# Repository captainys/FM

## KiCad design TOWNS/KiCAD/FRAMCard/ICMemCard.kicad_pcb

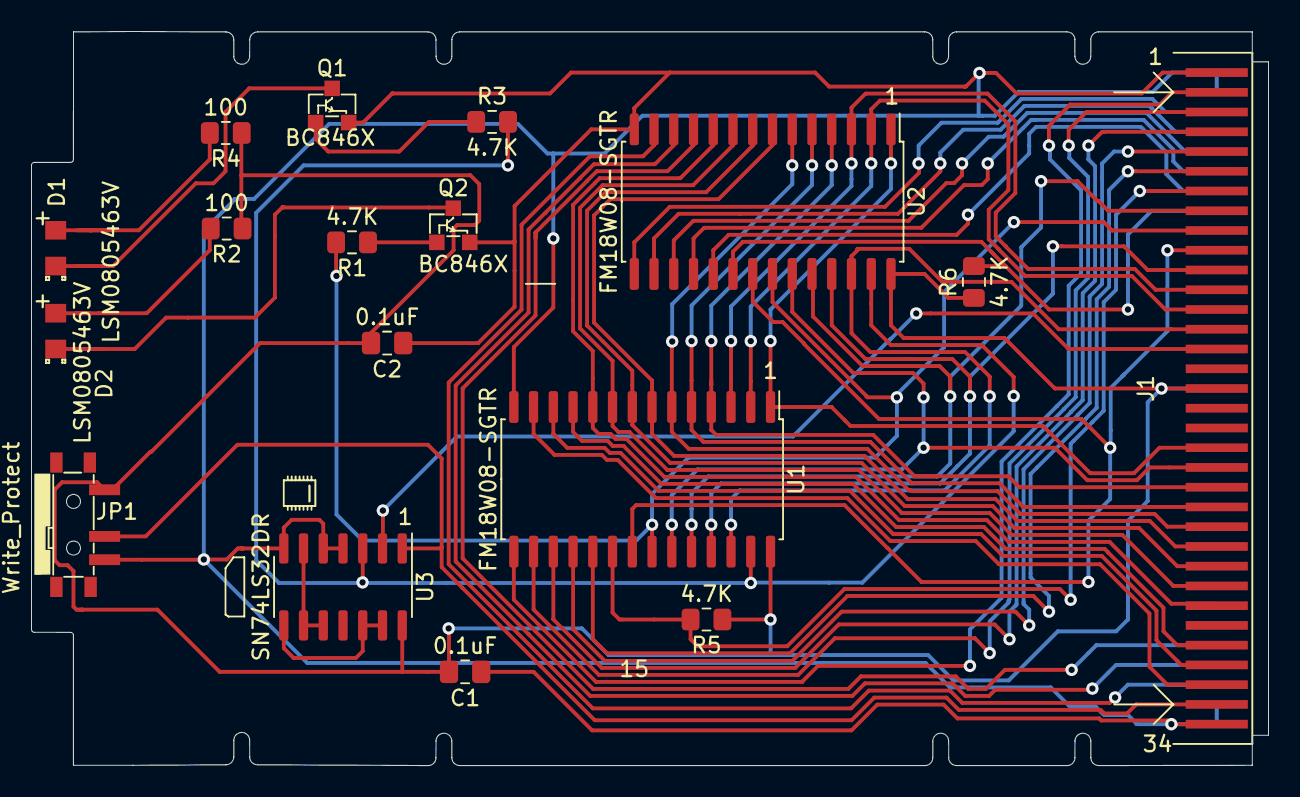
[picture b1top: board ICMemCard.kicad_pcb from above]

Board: 2 copper layers, 79.6 x 47.2 mm, 17 parts (0 on the bottom side), 47 nets.

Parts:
C1, C2: 0.1uF; C_0805_2012Metric_Pad1.18x1.45mm_HandSolder
D1, D2: LSM0805463V
J1: PCMCIA_Connector; PCMCIA_2x34_FrontBack
JP1: Write_Protect; MA_Memory_Card_Slide_Switch
Q1, Q2: BC846X; BC846X_AU_Q_NPN_BCE
R1, R3, R5, R6: 4.7K; R_0805_2012Metric_Pad1.15x1.40mm_HandSolder
R2, R4: 100; R_0805_2012Metric_Pad1.15x1.40mm_HandSolder
U1, U2: FM18W08-SGTR; SOIC-28W_7.5x17.9mm_P1.27mm
U3: SN74LS32DR; SOIC-14_3.9x8.7mm_P1.27mm

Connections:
/A1: J1.28, U1.10, U2.10
/A2: J1.27, U1.9, U2.9
/A3: J1.26, U1.8, U2.8
/A4: J1.25, U1.7, U2.7
/A5: J1.24, U1.6, U2.6
/A6: J1.23, U1.5, U2.5
/A7: J1.22, U1.4, U2.4
/A8: J1.12, U1.3, U2.3
/A9: J1.11, U1.25, U2.25
/A10: J1.8, U1.24, U2.24
/A11: J1.10, U1.21, U2.21
/A12: J1.21, U1.23, U2.23
/A13: J1.13, U1.2, U2.2
/A14: J1.14, U1.26, U2.26
/A15: J1.20, U1.1, U2.1
/D0: J1.30, U1.11
/D1: J1.31, U1.12
/D2: J1.32, U1.13
/D3: J1.2, U1.15
/D4: J1.3, U1.16
/D5: J1.4, U1.17
/D6: J1.5, U1.18
/D7: J1.6, U1.19
/D8: J1.64, U2.11
/D9: J1.65, U2.12
/D10: J1.66, U2.13
/D11: J1.37, U2.15
/D12: J1.38, U2.16
/D13: J1.39, U2.17
/D14: J1.40, U2.18
/D15: J1.41, U2.19
/WP: J1.33, JP1.2, U3.1
/~CE1: J1.7, R5.2, U1.20
/~CE2: J1.42, R6.2, U2.20
/~OE: J1.9, R1.2, U1.22, U2.22
/~WE: J1.15, U3.2
/~WEorWP: R3.2, U1.27, U2.27, U3.3
GND: C1.1, C2.1, J1.1, J1.34, J1.35, J1.36, J1.67, J1.68, JP1.1, Q1.3, Q2.3, U1.14, U2.14, U3.4, U3.5, U3.7
unnamed: D1.1, Q1.2
unnamed: D1.2, R4.2
unnamed: D2.1, Q2.2
unnamed: D2.2, R2.2
unnamed: Q1.1, R3.1
unnamed: Q2.1, R1.1
unnamed: U3.6, U3.9, U3.10
unnamed: U3.8, U3.12, U3.13
Vcc: C1.2, C2.2, J1.17, J1.51, JP1.3, R2.1, R4.1, R5.1, R6.1, U1.28, U2.28, U3.14

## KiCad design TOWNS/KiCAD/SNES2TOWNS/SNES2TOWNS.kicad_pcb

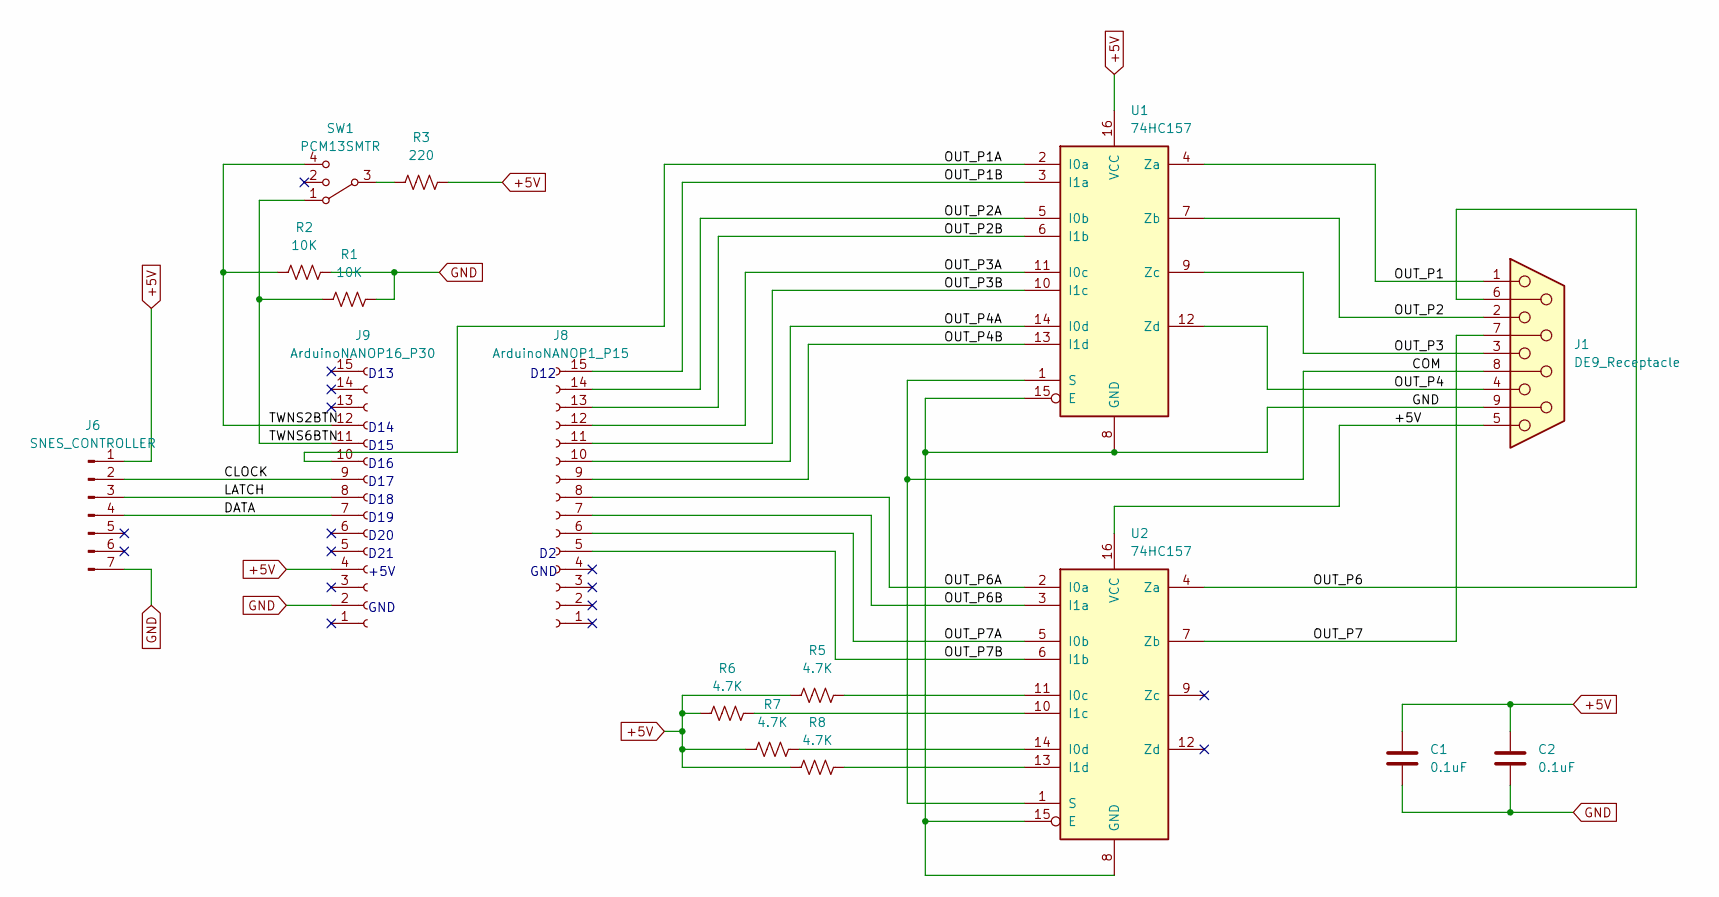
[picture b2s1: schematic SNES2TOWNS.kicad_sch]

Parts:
C1, C2: 0.1uF; C_0805_2012Metric_Pad1.18x1.45mm_HandSolder
J1: DE9_Receptacle; DSUB-9_Female_Vertical_P2.77x2.84mm
J6: SNES_CONTROLLER; SNES_Controller
J8: ArduinoNANOP1_P15; PinSocket_1x15_P2.54mm_Vertical
J9: ArduinoNANOP16_P30; PinSocket_1x15_P2.54mm_Vertical
R1, R2: 10K; R_0805_2012Metric_Pad1.20x1.40mm_HandSolder
R3: 220; R_0805_2012Metric_Pad1.20x1.40mm_HandSolder
R5, R6, R7, R8: 4.7K; R_0805_2012Metric_Pad1.20x1.40mm_HandSolder
SW1: PCM13SMTR; SW_SP3T_PCM13
U1, U2: 74HC157; DIP-16_W7.62mm_Socket

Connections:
+5V: C1.1, C2.1, J1.5, J6.1, J9.4, R3.2, R5.1, R6.1, R7.1, R8.1, U1.16 (VCC), U2.16 (VCC)
/CLOCK: J6.2, J9.9
/COM: J1.8, U1.1 (S), U2.1 (S)
/DATA: J6.4, J9.7
/LATCH: J6.3, J9.8
/OUT_P1: J1.1, U1.4 (Za)
/OUT_P1A: J9.10, U1.2 (I0a)
/OUT_P1B: J8.15, U1.3 (I1a)
/OUT_P2: J1.2, U1.7 (Zb)
/OUT_P2A: J8.14, U1.5 (I0b)
/OUT_P2B: J8.13, U1.6 (I1b)
/OUT_P3: J1.3, U1.9 (Zc)
/OUT_P3A: J8.12, U1.11 (I0c)
/OUT_P3B: J8.11, U1.10 (I1c)
/OUT_P4: J1.4, U1.12 (Zd)
/OUT_P4A: J8.10, U1.14 (I0d)
/OUT_P4B: J8.9, U1.13 (I1d)
/OUT_P6: J1.6, U2.4 (Za)
/OUT_P6A: J8.8, U2.2 (I0a)
/OUT_P6B: J8.7, U2.3 (I1a)
/OUT_P7: J1.7, U2.7 (Zb)
/OUT_P7A: J8.6, U2.5 (I0b)
/OUT_P7B: J8.5, U2.6 (I1b)
/TWNS2BTN: J9.12, R2.1, SW1.4
/TWNS6BTN: J9.11, R1.1, SW1.1
GND: C1.2, C2.2, J1.9, J6.7, J9.2, R1.2, R2.2, U1.8 (GND), U1.15 (E), U2.8 (GND), U2.15 (E)
unnamed: R3.1, SW1.3
unnamed: R5.2, U2.11 (I0c)
unnamed: R7.2, U2.14 (I0d)
unnamed: R6.2, U2.10 (I1c)
unnamed: R8.2, U2.13 (I1d)

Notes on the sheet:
GND
D20
D12
D19
D14
D16
D18
D13
D21
D17
+5V
D15

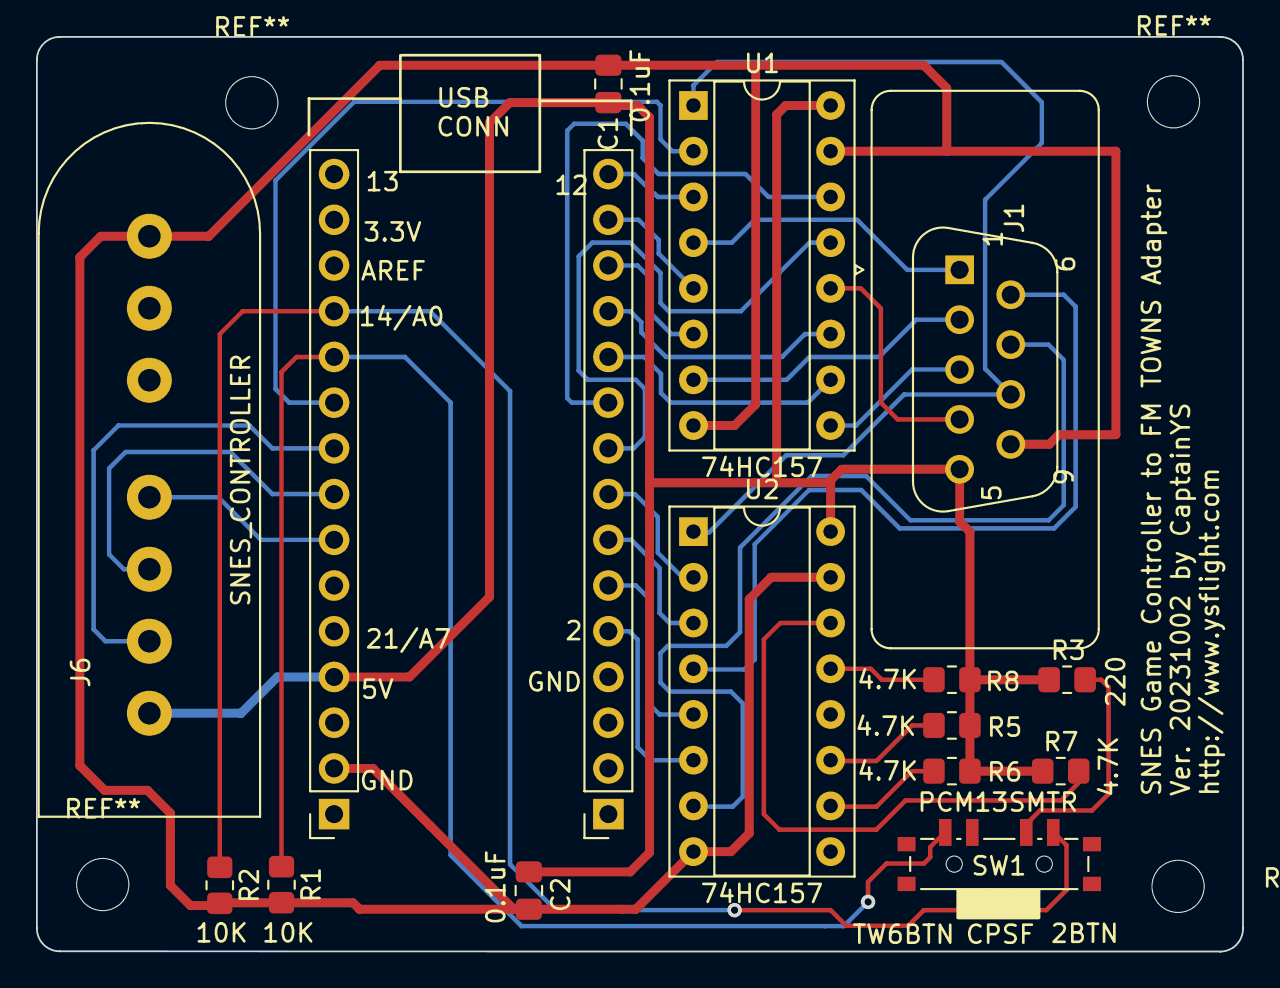
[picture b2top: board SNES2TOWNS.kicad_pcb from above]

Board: 2 copper layers, 67.0 x 50.8 mm, 16 parts (0 on the bottom side), 31 nets.

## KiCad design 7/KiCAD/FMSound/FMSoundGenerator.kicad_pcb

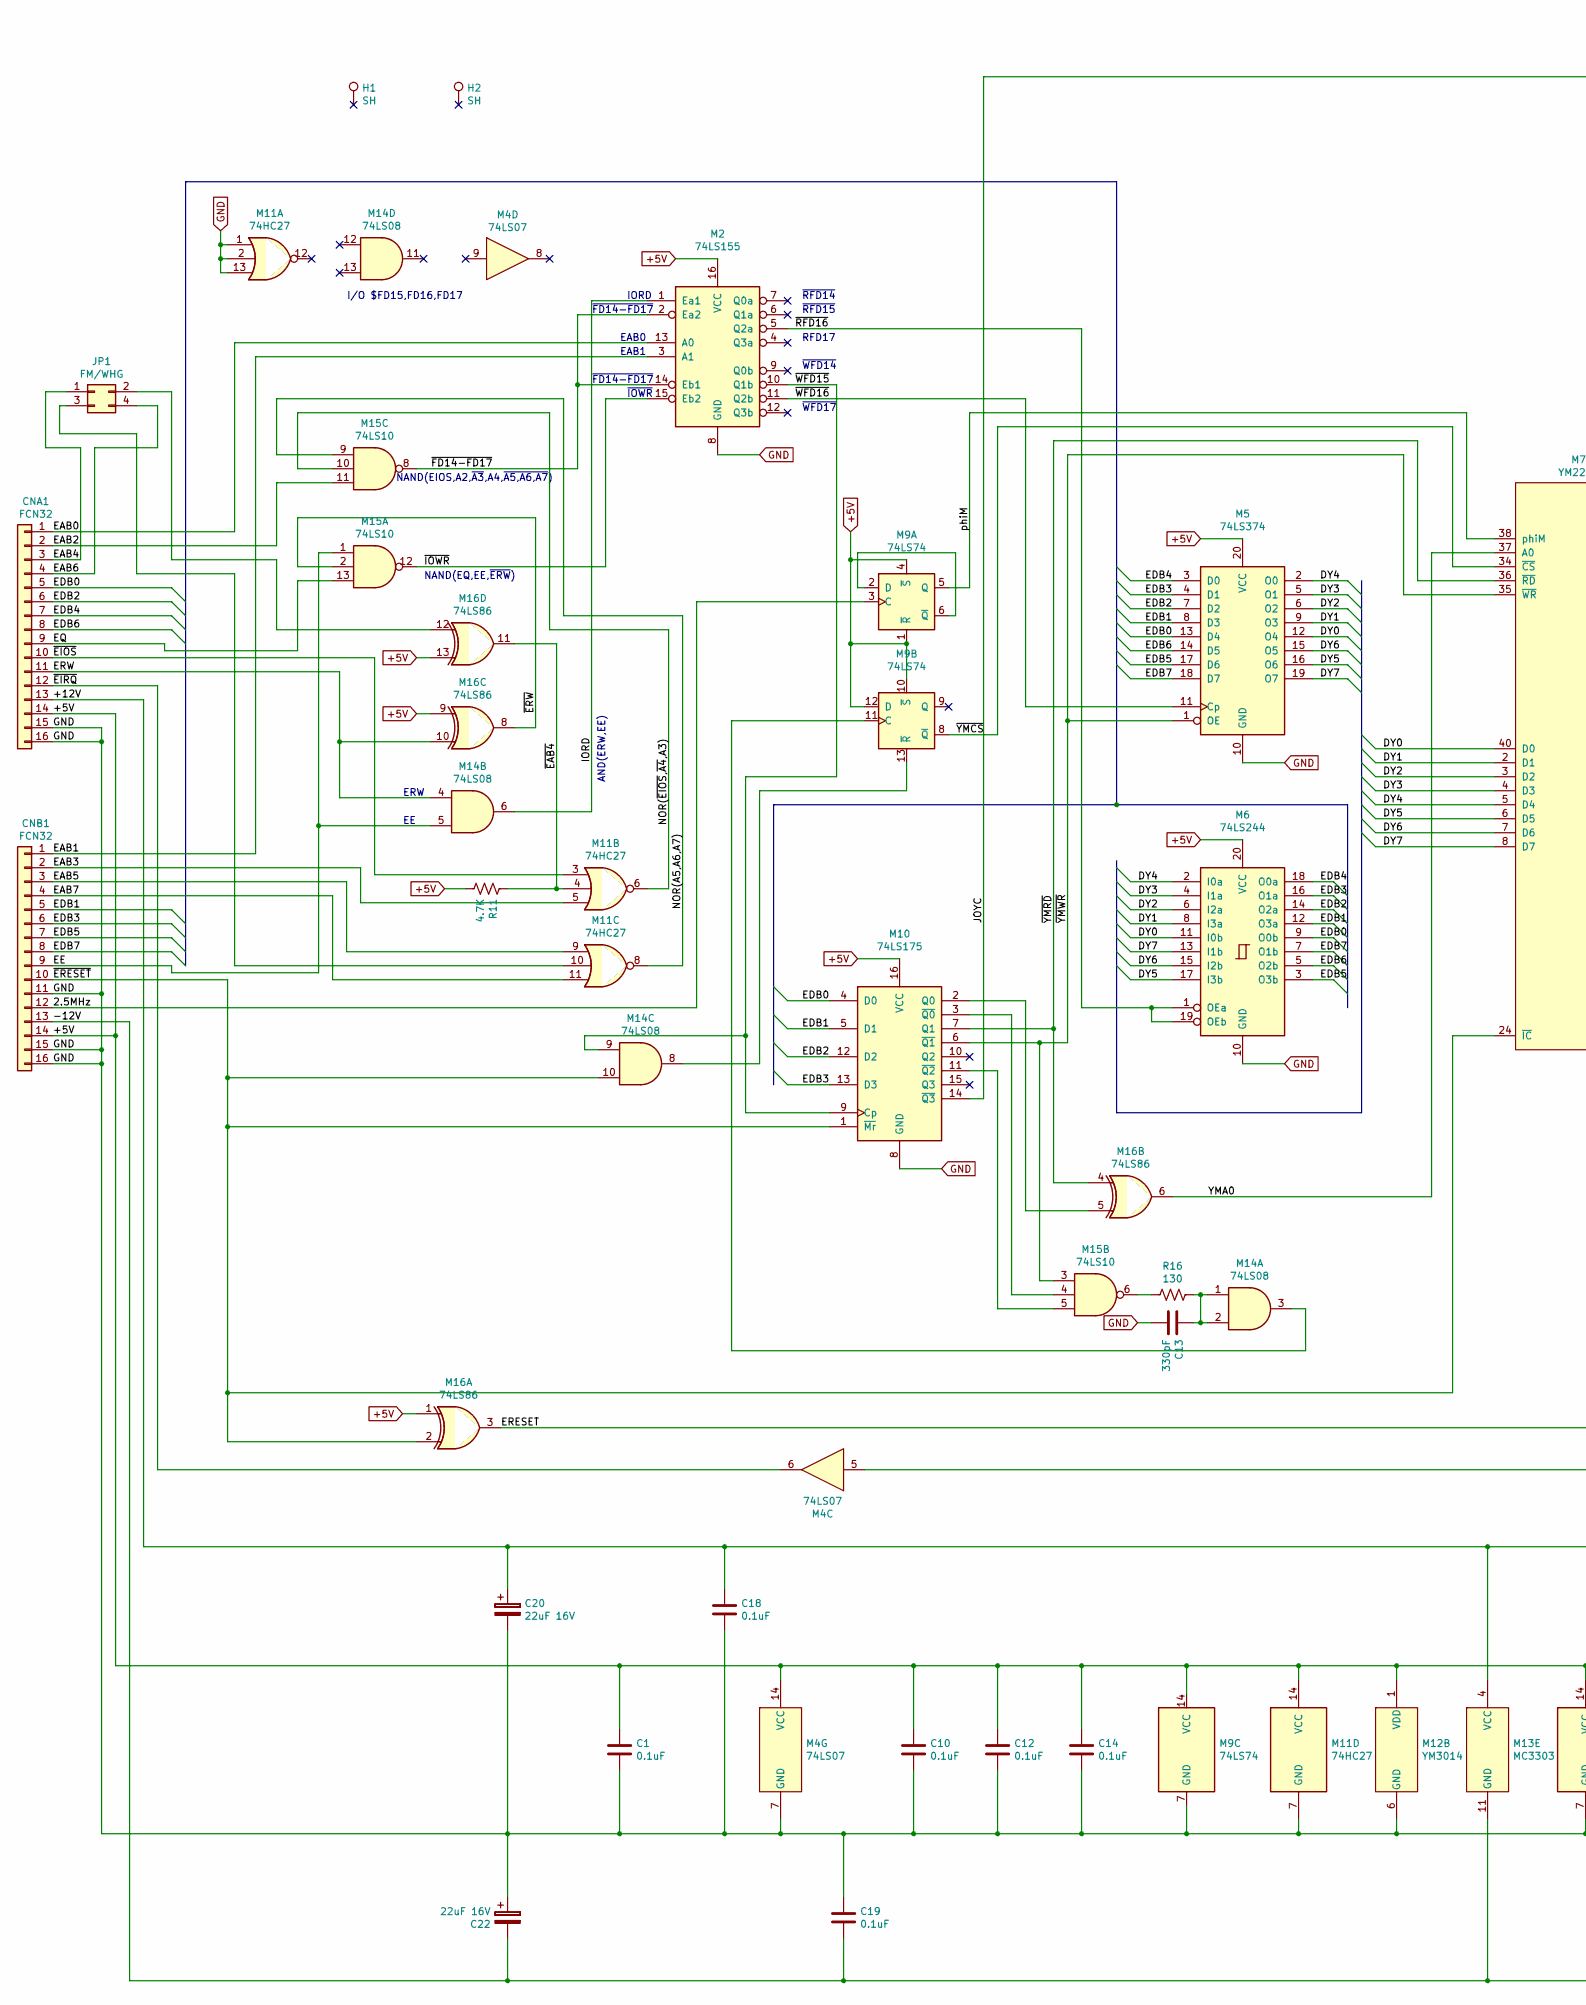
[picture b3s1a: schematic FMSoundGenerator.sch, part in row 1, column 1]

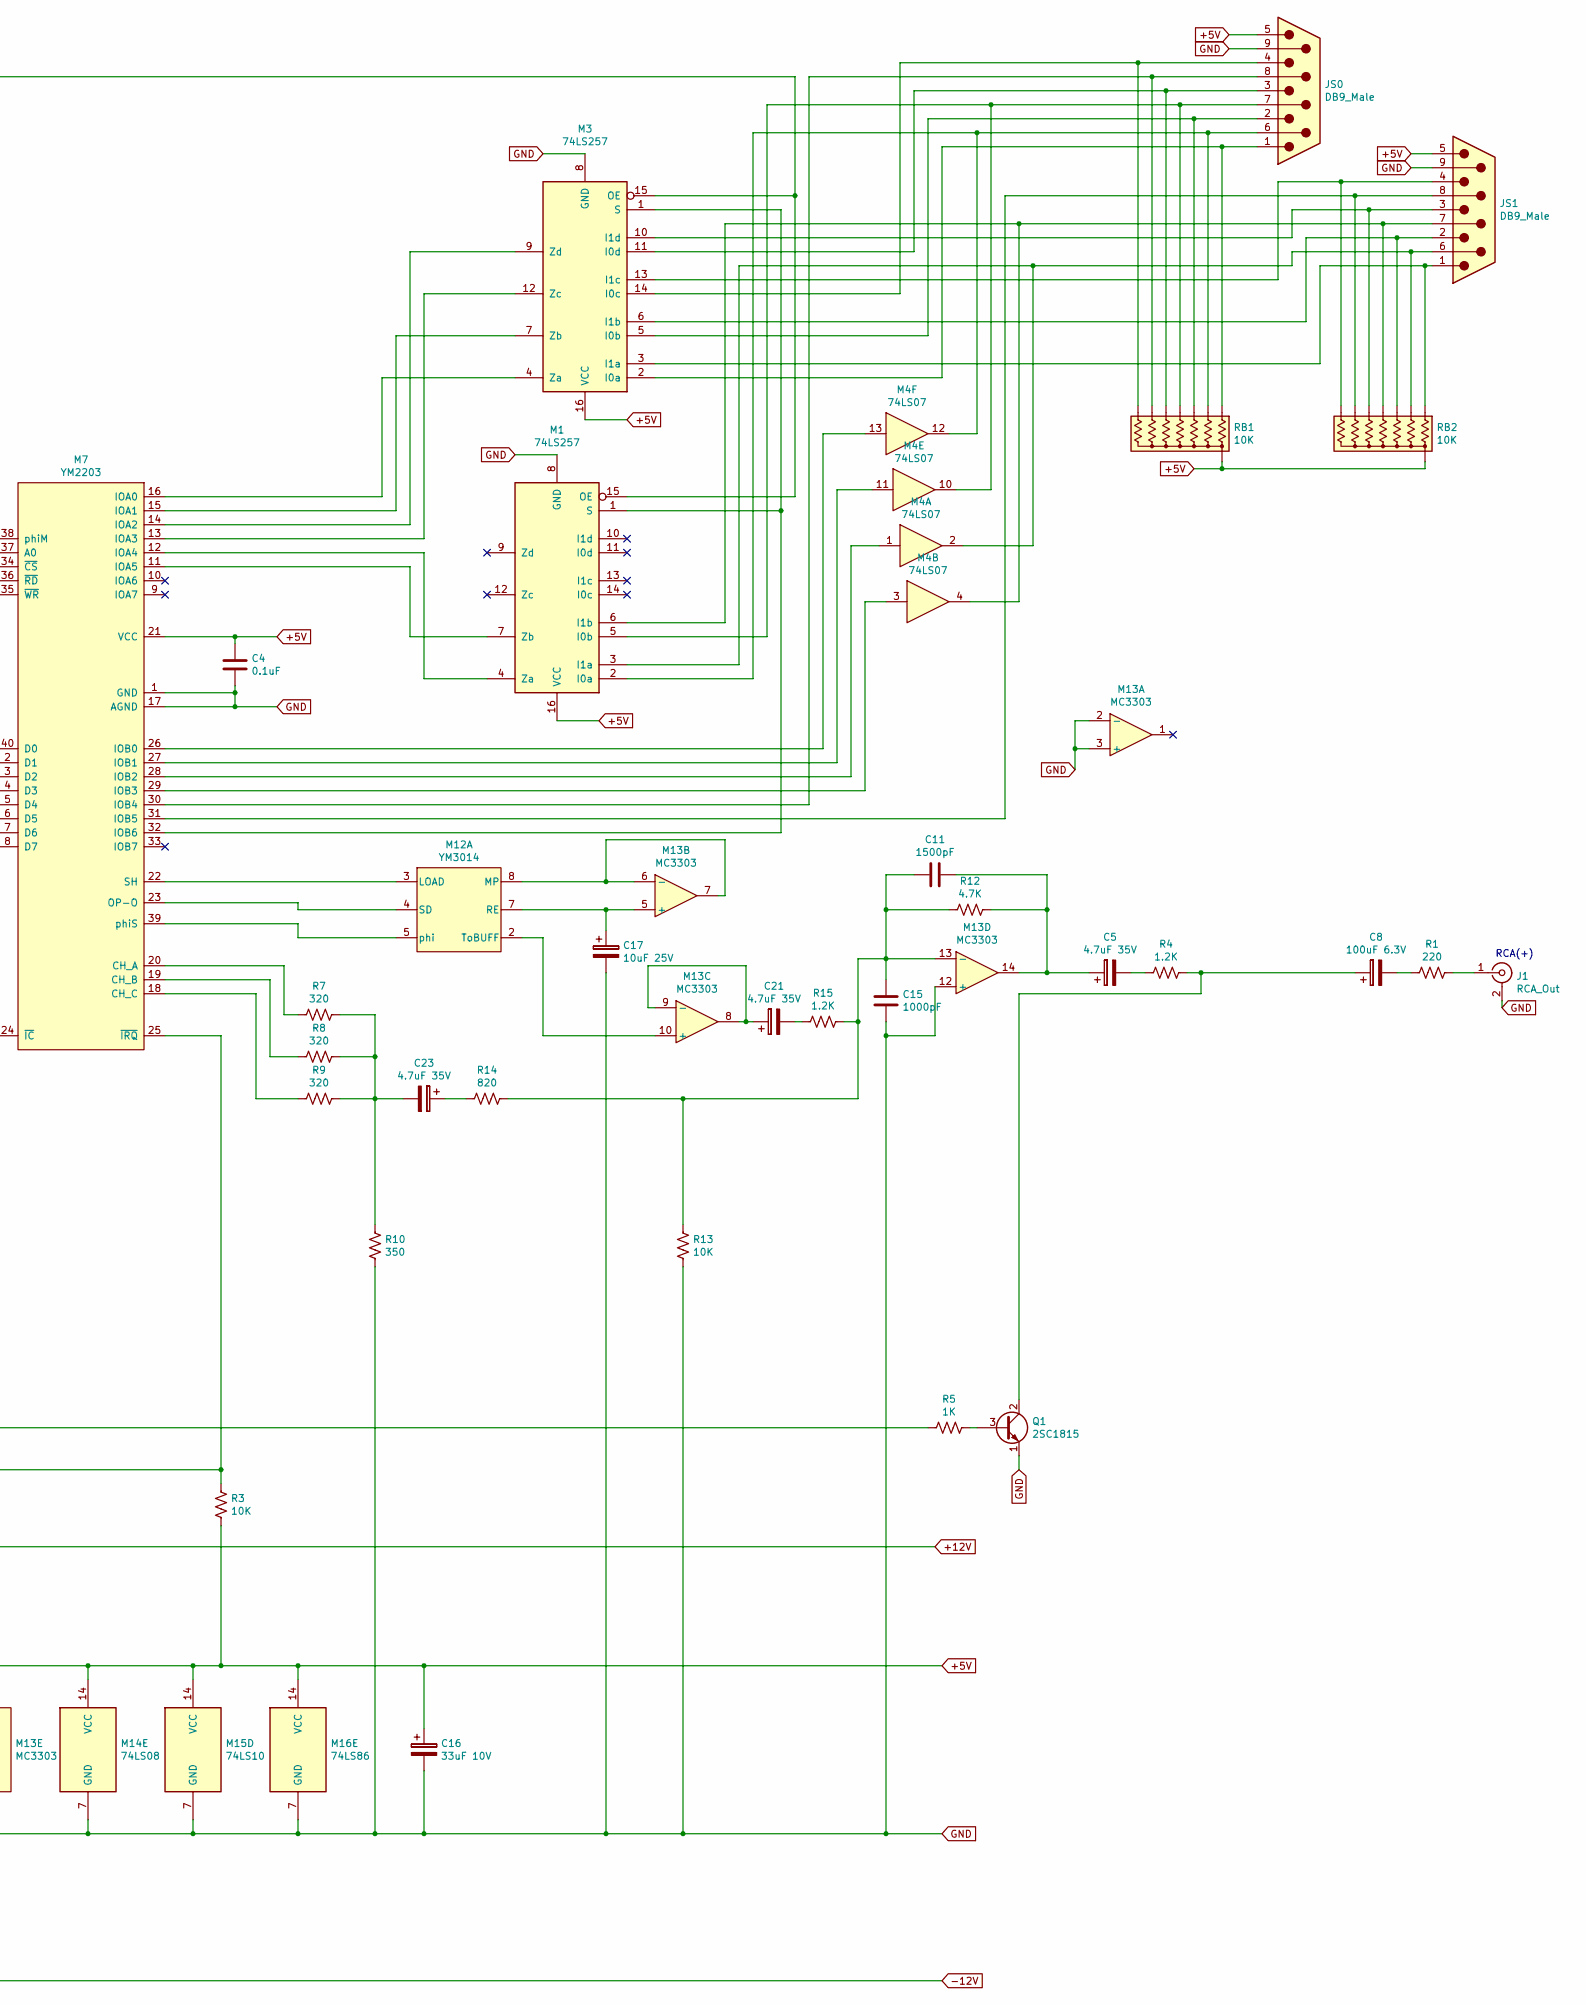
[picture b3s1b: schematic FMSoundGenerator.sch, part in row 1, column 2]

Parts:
C1, C4, C10, C12, C14, C18, C19: 0.1uF; C_Disc_D6.0mm_W2.5mm_P5.00mm
C5, C21, C23: 4.7uF 35V; CP_Radial_D5.0mm_P2.50mm
C8: 100uF 6.3V; CP_Radial_D5.0mm_P2.50mm
C11: 1500pF; C_Disc_D3.8mm_W2.6mm_P2.50mm
C13: 330pF; C_Disc_D3.8mm_W2.6mm_P2.50mm
C15: 1000pF; C_Disc_D3.8mm_W2.6mm_P2.50mm
C16: 33uF 10V; CP_Radial_D5.0mm_P2.50mm
C17: 10uF 25V; CP_Radial_D5.0mm_P2.50mm
C20, C22: 22uF 16V; CP_Radial_D5.0mm_P2.50mm
CNA1: FCN32; PinHeader_1x16_P2.54mm_Vertical
CNB1: FCN32; PinHeader_1x16_P2.54mm_Vertical
H1, H2: SH; TestPoint_Plated_Hole_D3.0mm
J1: RCA_Out; RCA Female
JP1: FM/WHG; PinHeader_2x02_P2.54mm_Vertical
JS0, JS1: DB9_Male; DSUB-9_Male_Vertical_P2.77x2.84mm_MountingHoles
M1, M3: 74LS257; DIP-16_W7.62mm_Socket
M2: 74LS155; DIP-16_W7.62mm_Socket
M4: 74LS07; DIP-14_W7.62mm_Socket
M5: 74LS374; DIP-20_W7.62mm_Socket
M6: 74LS244; DIP-20_W7.62mm_Socket
M7: YM2203; DIP-40_W15.24mm_Socket
M9: 74LS74; DIP-14_W7.62mm_Socket
M10: 74LS175; DIP-16_W7.62mm_Socket
M11: 74HC27; DIP-14_W7.62mm_Socket
M12: YM3014; DIP-8_W7.62mm_Socket
M13: MC3303; DIP-14_W7.62mm_Socket
M14: 74LS08; DIP-14_W7.62mm_Socket
M15: 74LS10; DIP-14_W7.62mm_Socket
M16: 74LS86; DIP-14_W7.62mm_Socket
Q1: 2SC1815; NPN_Transistor
R1: 220; R_Axial_DIN0207_L6.3mm_D2.5mm_P10.16mm_Horizontal
R3, R13: 10K; R_Axial_DIN0207_L6.3mm_D2.5mm_P10.16mm_Horizontal
R4, R15: 1.2K; R_Axial_DIN0207_L6.3mm_D2.5mm_P10.16mm_Horizontal
R5: 1K; R_Axial_DIN0207_L6.3mm_D2.5mm_P10.16mm_Horizontal
R7, R8, R9: 320; R_Axial_DIN0207_L6.3mm_D2.5mm_P10.16mm_Horizontal
R10: 350; R_Axial_DIN0207_L6.3mm_D2.5mm_P10.16mm_Horizontal
R11, R12: 4.7K; R_Axial_DIN0207_L6.3mm_D2.5mm_P10.16mm_Horizontal
R14: 820; R_Axial_DIN0207_L6.3mm_D2.5mm_P10.16mm_Horizontal
R16: 130; R_Axial_DIN0207_L6.3mm_D2.5mm_P10.16mm_Horizontal
RB1, RB2: 10K; R_Array_SIP8

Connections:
+5V: C1.1, C4.1, C10.1, C12.1, C14.1, C16.1, CNA1.14, CNB1.14, JS0.5, JS1.5, M1.16 (VCC), M2.16 (VCC), M3.16 (VCC), M4.14 (VCC), M5.20 (VCC), M6.20 (VCC), M7.21 (VCC), M9.1 (~R), M9.4 (~S), M9.10 (~S), M9.12 (D), M9.14 (VCC), M10.16 (VCC), M11.14 (VCC), M12.1 (VDD), M14.14 (VCC), M15.14 (VCC), M16.1, M16.9, M16.13, M16.14 (VCC), R3.2, R11.2, RB1.1 (common), RB2.1 (common)
+12V: C18.1, C20.1, CNA1.13, M13.4 (VCC)
-12V: C19.2, C22.2, CNB1.13, M13.11 (GND)
/2.5MHz: CNB1.12, M9.3 (C)
/DY0: M5.12 (O4), M6.11 (I0b), M7.40 (D0)
/DY1: M5.9 (O3), M6.8 (I3a), M7.2 (D1)
/DY2: M5.6 (O2), M6.6 (I2a), M7.3 (D2)
/DY3: M5.5 (O1), M6.4 (I1a), M7.4 (D3)
/DY4: M5.2 (O0), M6.2 (I0a), M7.5 (D4)
/DY5: M5.16 (O6), M6.17 (I3b), M7.6 (D5)
/DY6: M5.15 (O5), M6.15 (I2b), M7.7 (D6)
/DY7: M5.19 (O7), M6.13 (I1b), M7.8 (D7)
/EAB0: CNA1.1, M2.13 (A0)
/EAB1: CNB1.1, M2.3 (A1)
/EAB2: CNA1.2, M15.11
/EAB3: CNB1.2, M11.5
/EAB4: CNA1.3, JP1.1
/EAB5: CNB1.3, M11.9
/EAB6: CNA1.4, JP1.4
/EAB7: CNB1.4, M11.11
/EDB0: CNA1.5, M5.13 (D4), M6.9 (O0b), M10.4 (D0)
/EDB1: CNB1.5, M5.8 (D3), M6.12 (O3a), M10.5 (D1)
/EDB2: CNA1.6, M5.7 (D2), M6.14 (O2a), M10.12 (D2)
/EDB3: CNB1.6, M5.4 (D1), M6.16 (O1a), M10.13 (D3)
/EDB4: CNA1.7, M5.3 (D0), M6.18 (O0a)
/EDB5: CNB1.7, M5.17 (D6), M6.3 (O3b)
/EDB6: CNA1.8, M5.14 (D5), M6.5 (O2b)
/EDB7: CNB1.8, M5.18 (D7), M6.7 (O1b)
/EE: CNB1.9, M14.5, M15.1
/EQ: CNA1.9, M15.13
/ERESET: M16.3, R5.2
/ERW: CNA1.11, M14.4, M16.10
/IORD: M2.1 (Ea1), M14.6
/JOYC: M1.15 (OE), M3.15 (OE), M10.14 (~Q3)
/NOR(A5,A6,A7): M11.8, M15.9
/NOR(~EIOS~,~A4~,A3): M11.6, M15.10
/YMA0: M7.37 (A0), M16.6
/phiM: M7.38 (phiM), M9.5 (Q)
/~EAB4: M11.4, M16.11, R11.1
/~EIOS: CNA1.10, M11.3
/~EIRQ: CNA1.12, M4.6
/~ERESET: CNB1.10, M7.24 (~IC), M10.1 (~Mr), M14.10, M16.2
/~ERW: M15.2, M16.8
/~FD14-FD17: M2.2 (Ea2), M2.14 (Eb1), M15.8
/~IOWR: M2.15 (Eb2), M15.12
/~RFD16: M2.5 (Q2a), M6.1 (OEa), M6.19 (OEb)
/~WFD15: M2.10 (Q1b), M10.9 (Cp), M14.9
/~WFD16: M2.11 (Q2b), M5.11 (Cp)
/~YMCS: M7.34 (~CS), M9.8 (~Q)
/~YMRD: M7.36 (~RD), M10.7 (Q1), M16.4
/~YMWR: M5.1 (OE), M7.35 (~WR), M10.6 (~Q1), M15.3
GND: C1.2, C4.2, C10.2, C12.2, C13.2, C14.2, C15.2, C16.2, C17.2, C18.2, C19.1, C20.2, C22.1, CNA1.15, CNA1.16, CNB1.11, CNB1.15, CNB1.16, J1.2 (Ext), JS0.9, JS1.9, M1.8 (GND), M2.8 (GND), M3.8 (GND), M4.7 (GND), M5.10 (GND), M6.10 (GND), M7.1 (GND), M7.17 (AGND), M9.7 (GND), M10.8 (GND), M11.1, M11.2, M11.7 (GND), M11.13, M12.6 (GND), M13.2 (-), M13.3 (+), M13.12 (+), M14.7 (GND), M15.7 (GND), M16.7 (GND), Q1.1 (E), R10.1, R13.2
unnamed: C5.2, R4.1
unnamed: C8.1, Q1.2 (C), R4.2
unnamed: C8.2, R1.2
unnamed: C5.1, C11.1, M13.14, R12.1
unnamed: C11.2, C15.1, M13.13 (-), R12.2, R13.1, R14.1, R15.1
unnamed: C13.1, M14.1, M14.2, R16.1
unnamed: C17.1, M12.7 (RE), M13.5 (+)
unnamed: C21.1, M13.8, M13.9 (-)
unnamed: C21.2, R15.2
unnamed: C23.1, R14.2
unnamed: C23.2, R7.1, R8.1, R9.1, R10.2
unnamed: J1.1 (In), R1.1
unnamed: JP1.2, M16.12
unnamed: JP1.3, M11.10
unnamed: JS0.1, M3.2 (I0a), RB1.2 (R1)
unnamed: JS0.2, M3.5 (I0b), RB1.4 (R3)
unnamed: JS0.3, M3.11 (I0d), RB1.6 (R5)
unnamed: JS0.4, M3.14 (I0c), RB1.8 (R7)
unnamed: JS0.6, M1.2 (I0a), M4.12, RB1.3 (R2)
unnamed: JS0.7, M1.5 (I0b), M4.10, RB1.5 (R4)
unnamed: JS0.8, M7.30 (IOB4), RB1.7 (R6)
unnamed: JS1.1, M3.3 (I1a), RB2.2 (R1)
unnamed: JS1.2, M3.6 (I1b), RB2.4 (R3)
unnamed: JS1.3, M3.10 (I1d), RB2.6 (R5)
unnamed: JS1.4, M3.13 (I1c), RB2.8 (R7)
unnamed: JS1.6, M1.3 (I1a), M4.2, RB2.3 (R2)
unnamed: JS1.7, M1.6 (I1b), M4.4, RB2.5 (R4)
unnamed: JS1.8, M7.31 (IOB5), RB2.7 (R6)
unnamed: M1.1 (S), M3.1 (S), M7.32 (IOB6)
unnamed: M1.4 (Za), M7.12 (IOA4)
unnamed: M1.7 (Zb), M7.11 (IOA5)
unnamed: M3.4 (Za), M7.16 (IOA0)
unnamed: M3.7 (Zb), M7.15 (IOA1)
unnamed: M3.9 (Zd), M7.14 (IOA2)
unnamed: M3.12 (Zc), M7.13 (IOA3)
unnamed: M4.1, M7.28 (IOB2)
unnamed: M4.3, M7.29 (IOB3)
unnamed: M4.5, M7.25 (~IRQ), R3.1
unnamed: M4.11, M7.27 (IOB1)
unnamed: M4.13, M7.26 (IOB0)
unnamed: M7.18 (CH_C), R9.2
unnamed: M7.19 (CH_B), R8.2
unnamed: M7.20 (CH_A), R7.2
unnamed: M9.2 (D), M9.6 (~Q)
unnamed: M10.2 (Q0), M16.5
unnamed: M10.3 (~Q0), M15.4
unnamed: M10.11 (~Q2), M15.5
unnamed: M12.2 (ToBUFF), M13.10 (+)
unnamed: M7.22 (SH), M12.3 (LOAD)
unnamed: M7.23 (OP-O), M12.4 (SD)
unnamed: M7.39 (phiS), M12.5 (phi)
unnamed: M12.8 (MP), M13.6 (-), M13.7
unnamed: M9.11 (C), M14.3
unnamed: M9.13 (~R), M14.8
unnamed: M15.6, R16.2
unnamed: Q1.3 (B), R5.1

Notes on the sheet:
RCA(+)
EAB0
EAB1
I/O $FD15,FD16,FD17
ERW
AND(ERW,EE)
NAND(EQ,EE,~ERW~)
~IOWR
IORD
~FD14-FD17
NAND(EIOS,A2,~A3~,A4,~A5,A6,A7~)
~RFD14
~RFD15
RFD17
~WFD14
~WFD17

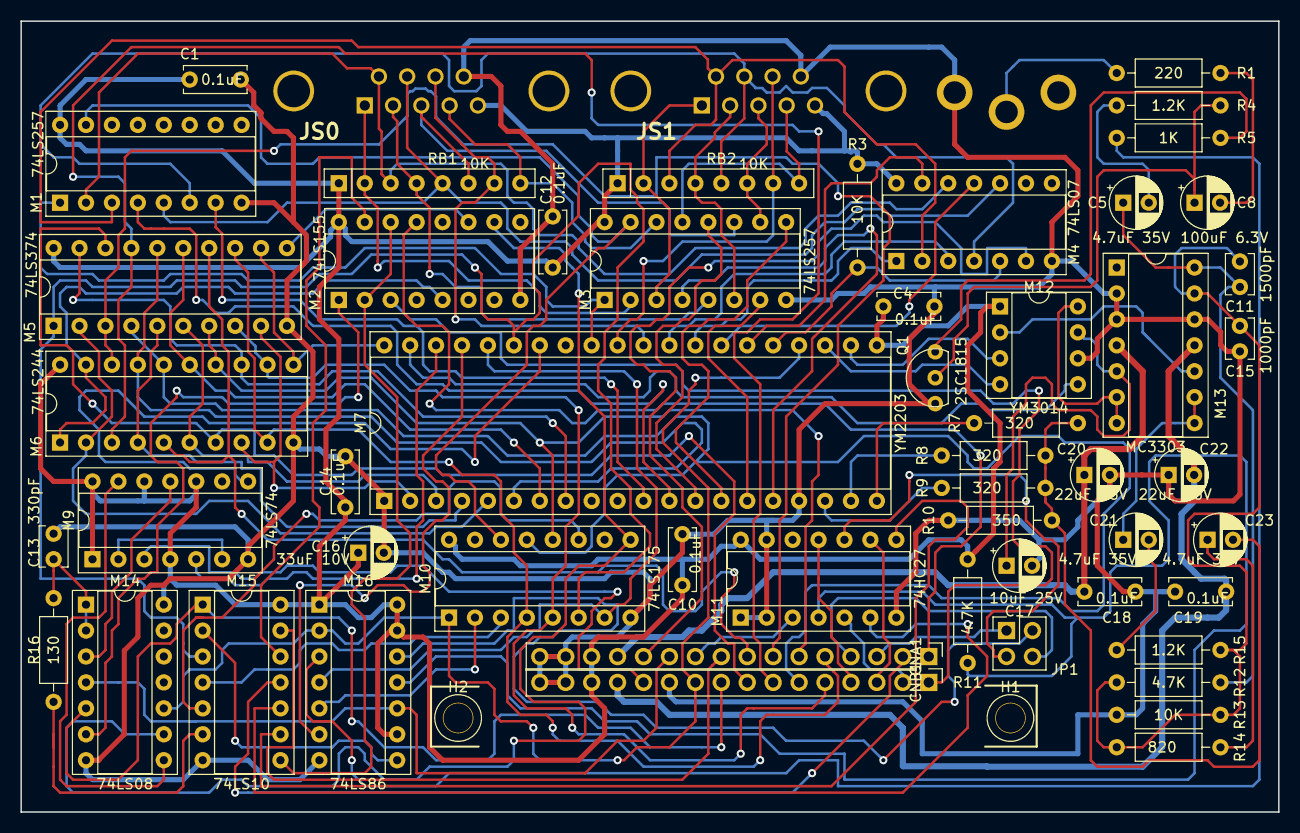
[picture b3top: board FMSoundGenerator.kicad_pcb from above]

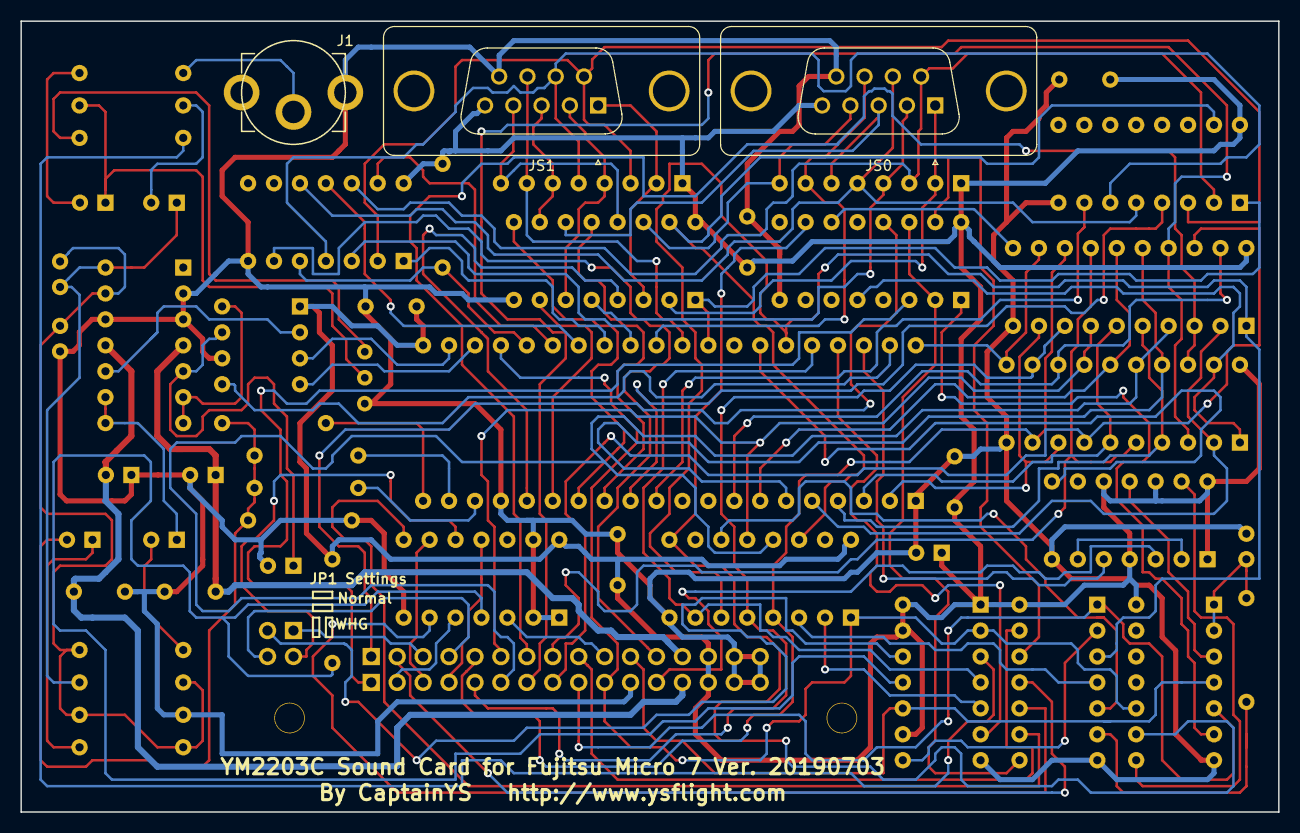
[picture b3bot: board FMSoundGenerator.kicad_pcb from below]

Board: 2 copper layers, 123.2 x 77.5 mm, 58 parts (3 on the bottom side), 108 nets.
